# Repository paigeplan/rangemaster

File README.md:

eagle files I made for the rangemaster schematic found here: http://fuzzcentral.ssguitar.com/rangemaster.php

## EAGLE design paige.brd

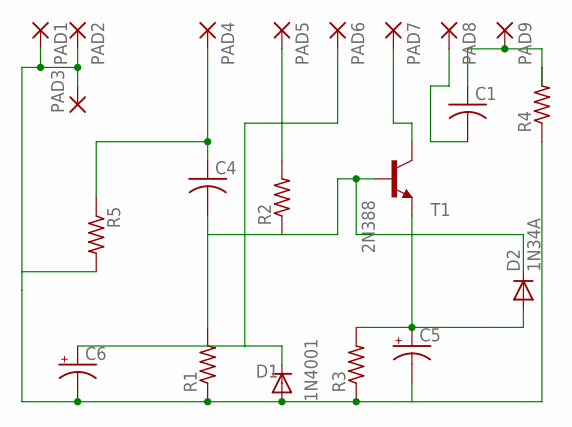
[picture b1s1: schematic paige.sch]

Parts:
C1: C-US025-050X050; C025-050X050
C4: C-US075-032X103; C075-032X103
C5, C6: CPOL-USE2.5-7; E2,5-7
D1: 1N4001; DO41-10
D2: 1N34A; DO41-10
PAD1, PAD2, PAD3, PAD4, PAD5, PAD6, PAD7, PAD8, PAD9: 1,6/0,9
R1, R2, R3, R4, R5: R-US_0207/5V; 0207/5V
T1: 2N388; TO92-EBC-OVAL

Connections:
unnamed: C4.1, PAD4.1, R5.1
unnamed: C4.2, D2.C, R1.2, R2.1, T1.B
unnamed: C6.+, D1.C, PAD5.1, PAD6.1, R2.2
unnamed: C5.+, D2.A, R3.2, T1.E
unnamed: C1.1, PAD9.1, R4.2
unnamed: C5.-, C6.-, D1.A, PAD1.1, PAD2.1, PAD3.1, R1.1, R3.1, R4.1, R5.2
unnamed: PAD7.1, T1.C
unnamed: C1.2, PAD8.1

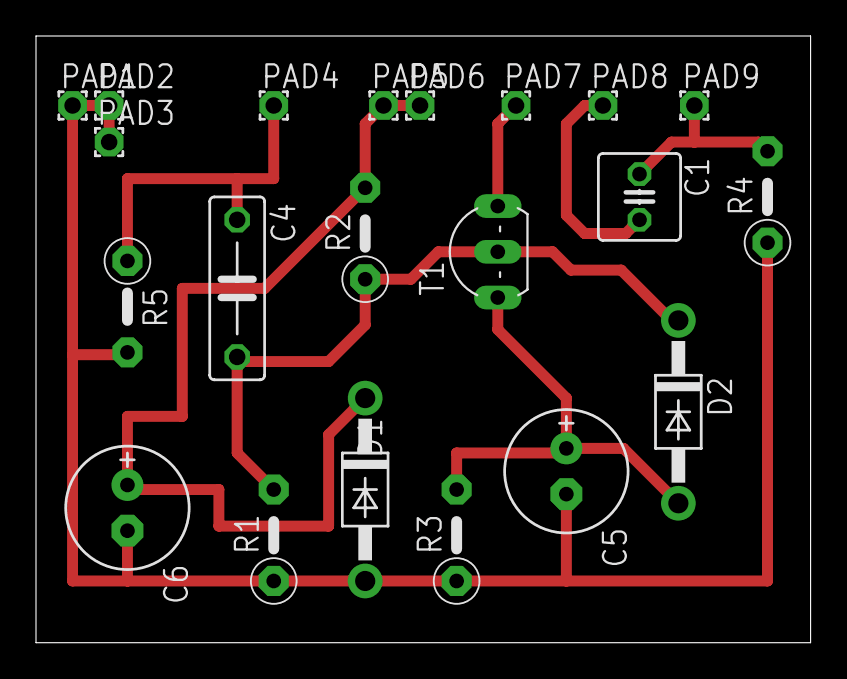
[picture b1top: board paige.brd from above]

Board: 2 copper layers, 43.0 x 33.7 mm, 21 parts (0 on the bottom side), 8 nets.

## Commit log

2018-12-11 adding proj files
2018-12-11 add README
